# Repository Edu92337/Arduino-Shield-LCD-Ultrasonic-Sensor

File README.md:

# Shield Arduino com LCD, Potenciômetro e Sensor Ultrassônico

## Descrição
Este projeto utiliza uma shield simples para Arduino equipada com um display LCD, um potenciômetro e um sensor ultrassônico. Ele mede a distância usando o sensor ultrassônico e exibe os dados em tempo real no LCD. O potenciômetro permite ajustar o brilho do display.

## Componentes Utilizados
- Arduino UNO
- Display LCD 16x2
- Potenciômetro de 10kΩ
- Sensor Ultrassônico HC-SR04

## Funcionalidades
- **Medição de Distância**: O sensor ultrassônico mede a distância até um objeto e exibe o valor no LCD.
- **Ajuste de Brilho**: O potenciômetro controla o brilho do LCD.

## Como Usar
1. Conecte os componentes conforme o diagrama.
2. Baixe o esquematico e a board da shield para o Eagle.
3. Carregue o código `codigoShield.ino`  para o Arduino.

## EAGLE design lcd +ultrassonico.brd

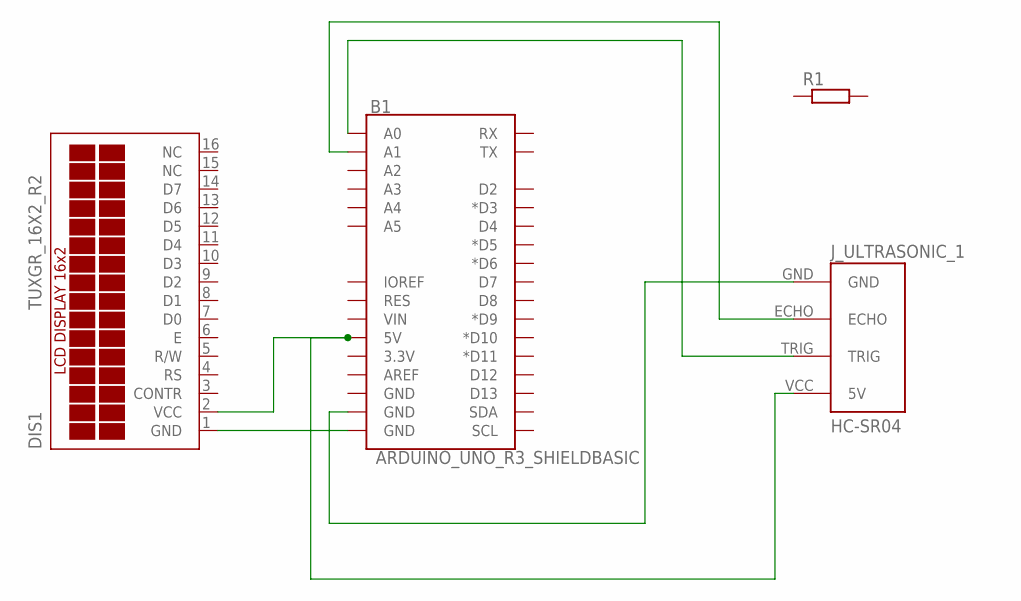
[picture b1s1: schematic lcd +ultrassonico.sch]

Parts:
B1: ARDUINO_UNO_R3_SHIELDBASIC; UNO_R3_SHIELD
DIS1: TUXGR_16X2_R2
J_ULTRASONIC_1: HC-SR04; HC-SR04_FOOTPRINT
R1: R-EU_0204/7; 0204/7

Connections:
unnamed: B1.GND@0 (GND), DIS1.1 (GND)
unnamed: B1.5V, DIS1.2 (VCC), J_ULTRASONIC_1.VCC (5V)
unnamed: B1.GND@1 (GND), J_ULTRASONIC_1.GND
unnamed: B1.A0, J_ULTRASONIC_1.TRIG
unnamed: B1.A1, J_ULTRASONIC_1.ECHO

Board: 2 copper layers, 4 parts (0 on the bottom side), 5 nets, no tracks yet.

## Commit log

2024-11-12 Rename ultrassonicoElcd.ino to codigoShield.ino
2024-11-12 Rename Captura de tela 2024-11-12 191556.png to diagrama_tinkercad.png

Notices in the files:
parts and their libraries:
SparkFun-Boards: Licensing: Creative Commons ShareAlike 4.0 International - https://creativecommons.org/licenses/by-sa/4.0
